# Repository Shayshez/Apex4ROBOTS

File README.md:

# Apex4ROBOTS
1u Peaks for Intellijel format

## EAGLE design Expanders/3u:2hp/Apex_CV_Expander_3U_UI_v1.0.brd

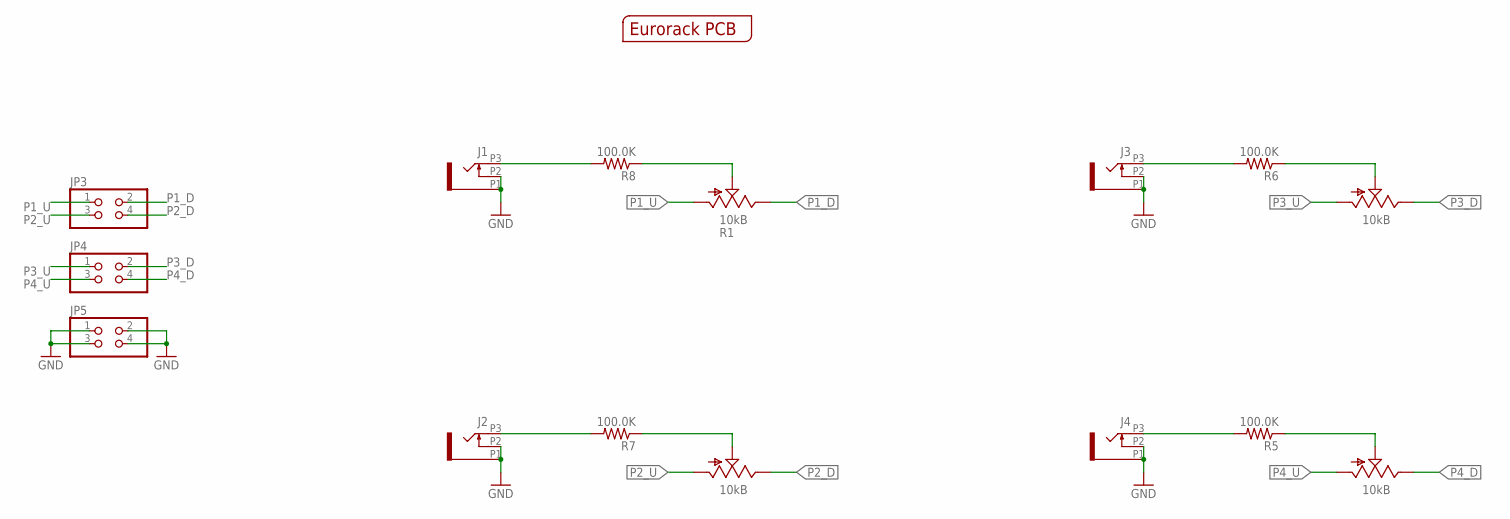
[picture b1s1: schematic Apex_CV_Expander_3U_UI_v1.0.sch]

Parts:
J1, J2, J3, J4: OG-PJ301_PJ301_THONKICONN7; OG-PJ301_WQP_PJ_301M7
JP3, JP4, JP5: PINHD-2X2; 2X02
PCB1: EURORACK_PCB2HP; EURORACK2HPPCB
R1, R2, R3, R4: 10kB; POTS_TALL_TRIMMER_POT_VERTICAL_SLOTED
R5, R6, R7, R8: 100.0K; R0603

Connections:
GND: J1.P1 (1), J1.P2 (2), J2.P1 (1), J2.P2 (2), J3.P1 (1), J3.P2 (2), J4.P1 (1), J4.P2 (2), JP5.1, JP5.2, JP5.3, JP5.4
unnamed: J1.P3 (3), R8.2
unnamed: R1.P$2 (S), R8.1
unnamed: J2.P3 (3), R7.2
unnamed: R2.P$2 (S), R7.1
unnamed: J3.P3 (3), R6.2
unnamed: R3.P$2 (S), R6.1
unnamed: J4.P3 (3), R5.2
unnamed: R4.P$2 (S), R5.1
P1_D: JP3.2, R1.P$1 (E)
P1_U: JP3.1, R1.P$3 (A)
P2_D: JP3.4, R2.P$1 (E)
P2_U: JP3.3, R2.P$3 (A)
P3_D: JP4.2, R3.P$1 (E)
P3_U: JP4.1, R3.P$3 (A)
P4_D: JP4.4, R4.P$1 (E)
P4_U: JP4.3, R4.P$3 (A)

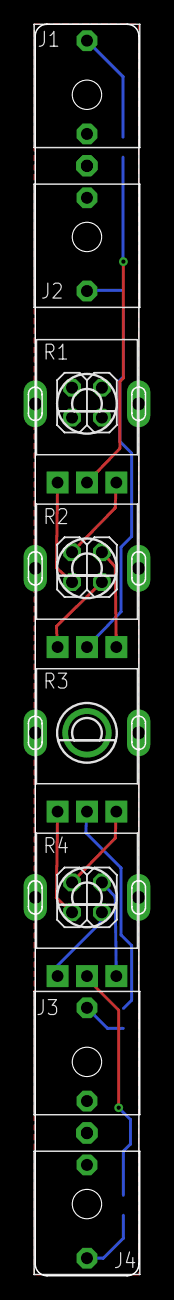
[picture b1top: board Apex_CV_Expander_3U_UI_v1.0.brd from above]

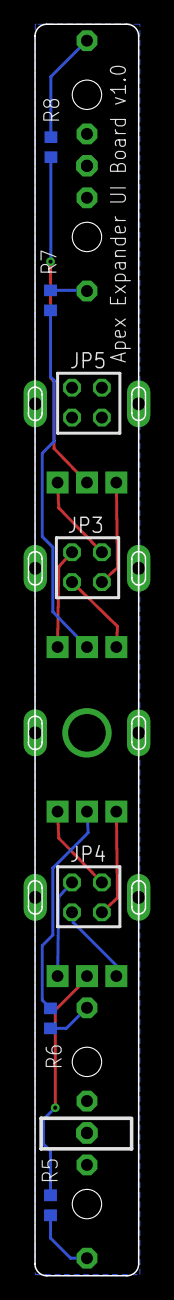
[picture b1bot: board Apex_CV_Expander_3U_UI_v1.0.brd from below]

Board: 2 copper layers, 10.0 x 106.5 mm, 16 parts (4 on the bottom side), 17 nets.

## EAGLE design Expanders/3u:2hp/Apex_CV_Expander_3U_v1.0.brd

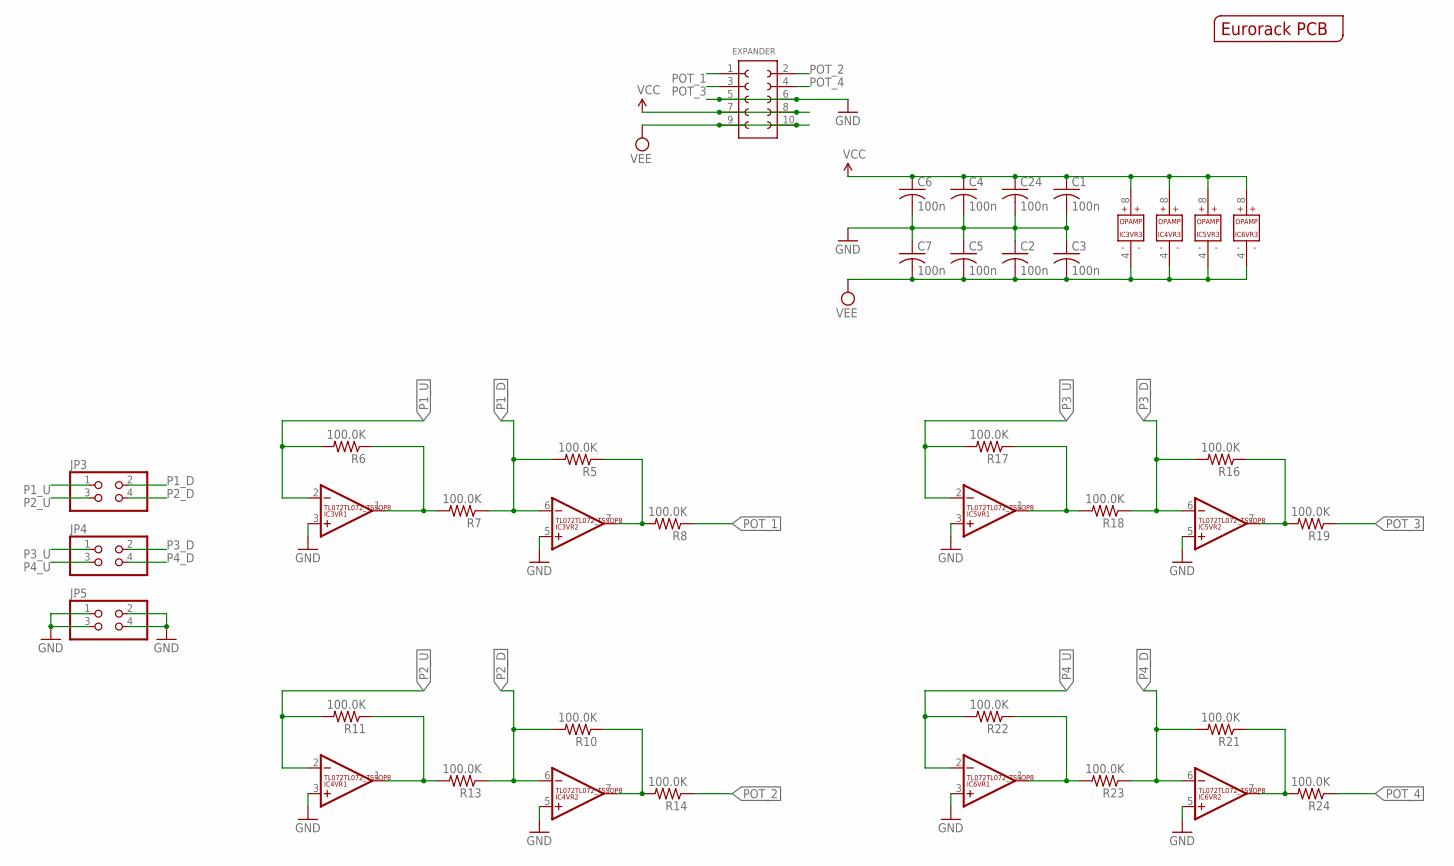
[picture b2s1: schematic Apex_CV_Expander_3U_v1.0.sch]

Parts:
C1, C2, C3, C4, C5, C6, C7, C24: 100n; C0603
EXPANDER: 61301021121
IC3, IC4, IC5, IC6: TL072TL072_TSSOP8; TL072_TSSOP8
JP3, JP4, JP5: PINHD-2X2; 2X02
PCB1: EURORACK_PCB2HP; EURORACK2HPPCB
R5, R6, R7, R8, R10, R11, R13, R14, R16, R17, R18, R19, R21, R22, R23, R24: 100.0K; R0603

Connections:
GND: C1.2, C2.1, C3.1, C4.2, C5.1, C6.2, C7.1, C24.2, EXPANDER.5 (3), EXPANDER.6 (8), IC3.3 (+IN), IC3.5 (+IN), IC4.3 (+IN), IC4.5 (+IN), IC5.3 (+IN), IC5.5 (+IN), IC6.3 (+IN), IC6.5 (+IN), JP5.1, JP5.2, JP5.3, JP5.4
unnamed: IC3.7 (OUT), R5.1, R8.2
unnamed: IC3.1 (OUT), R6.1, R7.2
unnamed: IC4.7 (OUT), R10.1, R14.2
unnamed: IC4.1 (OUT), R11.1, R13.2
unnamed: IC5.7 (OUT), R16.1, R19.2
unnamed: IC5.1 (OUT), R17.1, R18.2
unnamed: IC6.7 (OUT), R21.1, R24.2
unnamed: IC6.1 (OUT), R22.1, R23.2
P1_D: IC3.6 (-IN), JP3.2, R5.2, R7.1
P1_U: IC3.2 (-IN), JP3.1, R6.2
P2_D: IC4.6 (-IN), JP3.4, R10.2, R13.1
P2_U: IC4.2 (-IN), JP3.3, R11.2
P3_D: IC5.6 (-IN), JP4.2, R16.2, R18.1
P3_U: IC5.2 (-IN), JP4.1, R17.2
P4_D: IC6.6 (-IN), JP4.4, R21.2, R23.1
P4_U: IC6.2 (-IN), JP4.3, R22.2
POT_1: EXPANDER.1, R8.1
POT_2: EXPANDER.2 (10), R14.1
POT_3: EXPANDER.3 (2), R19.1
POT_4: EXPANDER.4 (9), R24.1
VCC: C1.1, C4.1, C6.1, C24.1, EXPANDER.7 (4), EXPANDER.8 (7), IC3.8 (V+), IC4.8 (V+), IC5.8 (V+), IC6.8 (V+)
VEE: C2.2, C3.2, C5.2, C7.2, EXPANDER.9 (5), EXPANDER.10 (6), IC3.4 (V-), IC4.4 (V-), IC5.4 (V-), IC6.4 (V-)

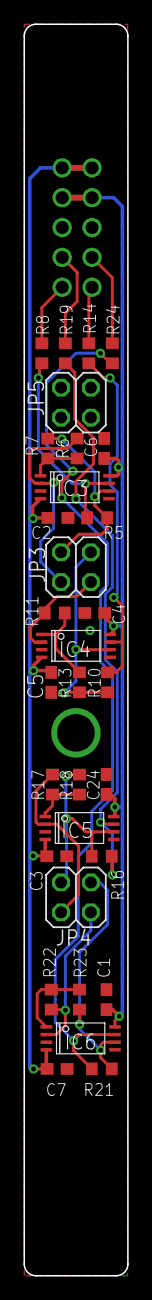
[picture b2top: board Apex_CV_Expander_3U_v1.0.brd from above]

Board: 2 copper layers, 8.8 x 106.5 mm, 33 parts (1 on the bottom side), 23 nets.

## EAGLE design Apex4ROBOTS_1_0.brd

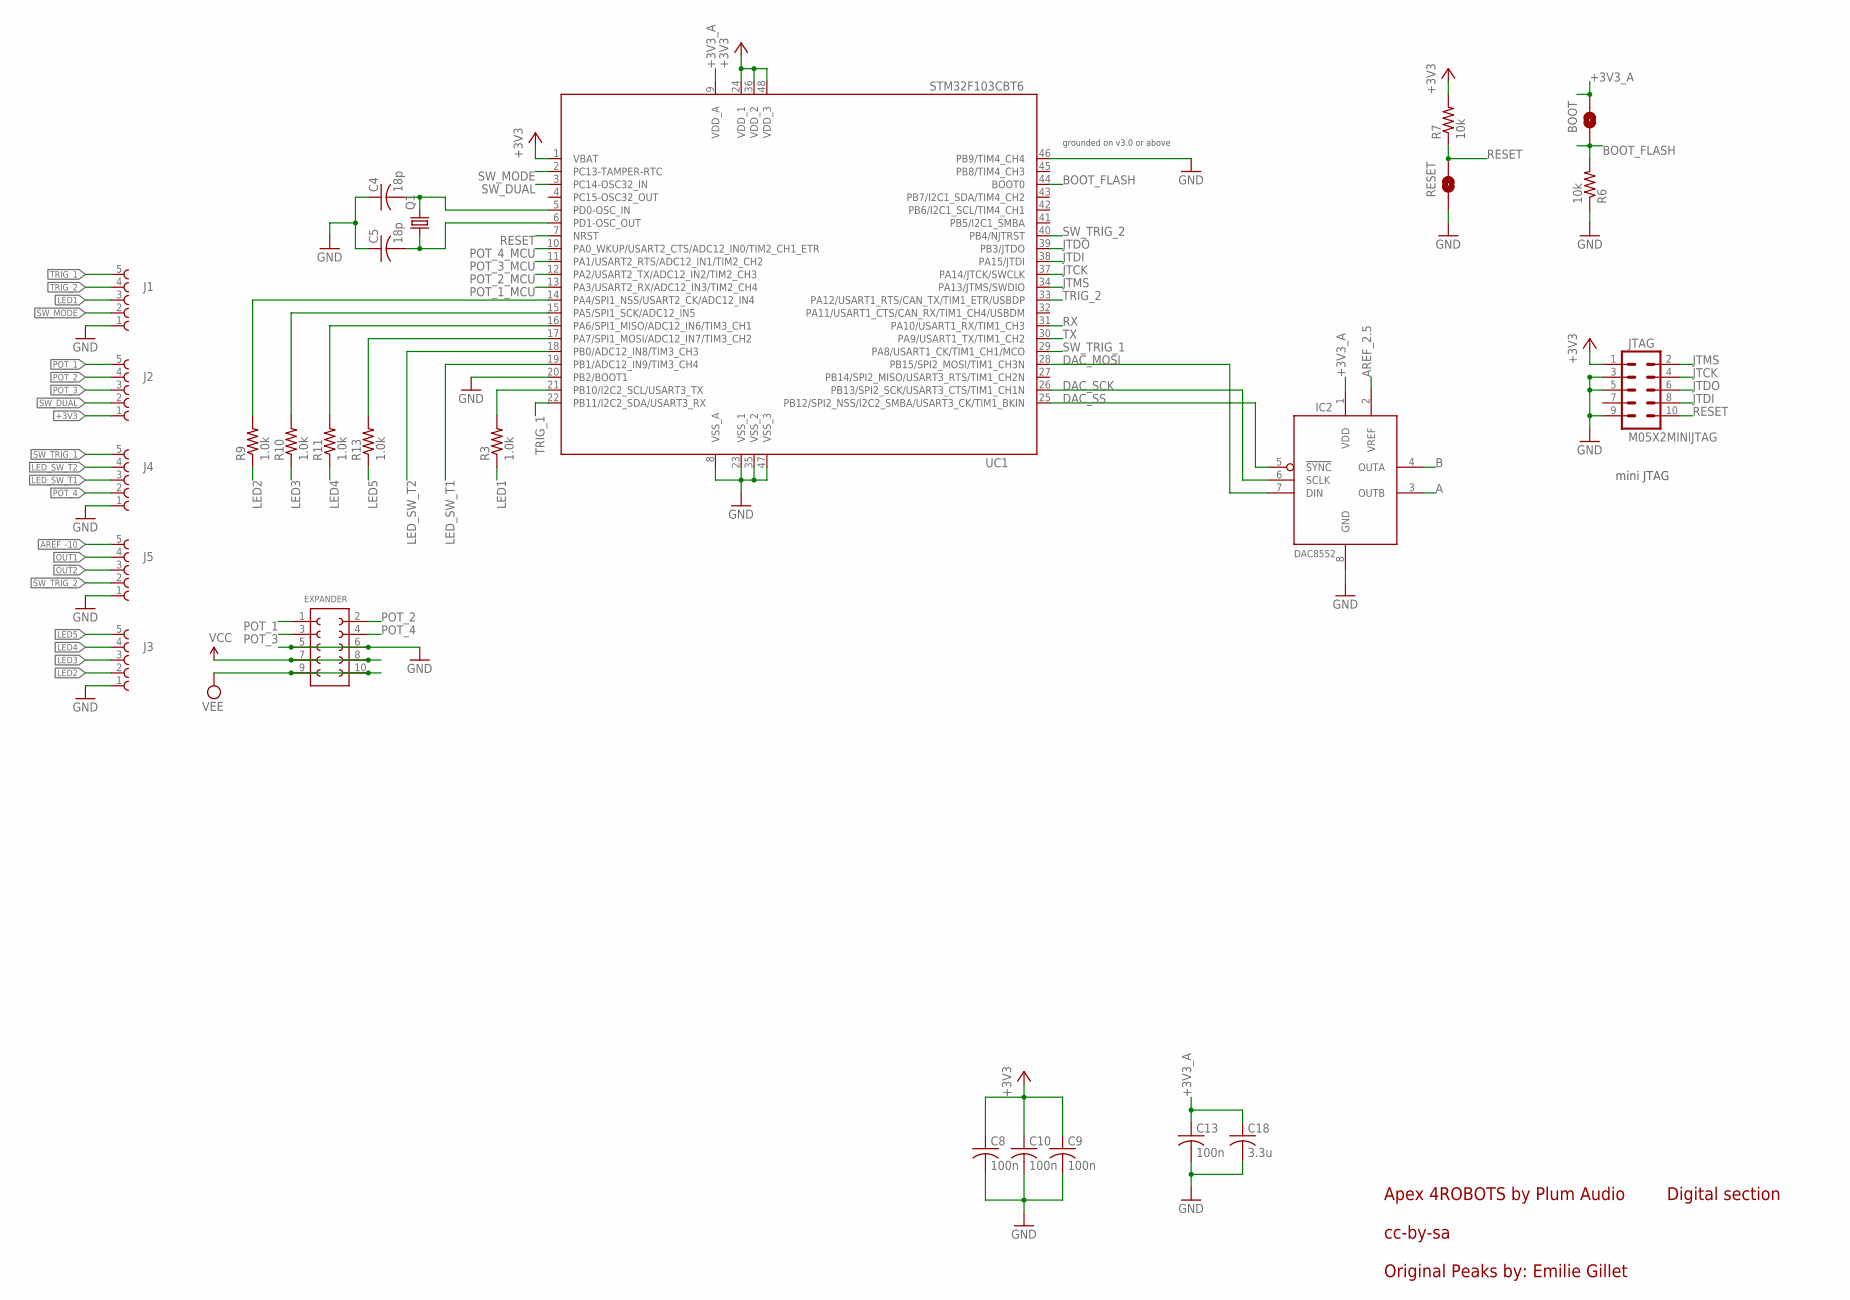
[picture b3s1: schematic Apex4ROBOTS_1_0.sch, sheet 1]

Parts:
BOOT: BOOT; SMT-JUMPER_2_NO_SILK
C4, C5: 18p; C0603
C8, C9, C10, C13: 100n; C0603
C18: 3.3u; C0603
EXPANDER: 61301021121
IC2: DAC8552; MSOP-8
J1, J2, J3, J4, J5: 61300511121
JTAG: M05X2MINIJTAG; 2X5-1.27
Q1: CRYSTAL7A; XTAL500X320X120
R3, R9, R10, R11, R13: 1.0k; R0603
R6, R7: 10k; R0603
RESET: RESET; SMT-JUMPER_2_NO_SILK
UC1: STM32F103CBT6; LQFP48

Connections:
+3V3: C8.1, C9.1, C10.1, J2.1 (5), JTAG.1, R7.2, UC1.1 (VBAT), UC1.24 (VDD_1), UC1.36 (VDD_2), UC1.48 (VDD_3); also elsewhere on the board
+3V3_A: BOOT.2, C13.1, C18.1, IC2.1 (VDD), UC1.9 (VDD_A); also elsewhere on the board
A: IC2.3 (OUTB); also elsewhere on the board
AREF_2.5: IC2.2 (VREF); also elsewhere on the board
AREF_-10: J5.5 (1); also elsewhere on the board
B: IC2.4 (OUTA); also elsewhere on the board
BOOT_FLASH: BOOT.1, R6.2, UC1.44 (BOOT0)
DAC_MOSI: IC2.7 (DIN), UC1.28 (PB15/SPI2_MOSI/TIM1_CH3N)
DAC_SCK: IC2.6 (SCLK), UC1.26 (PB13/SPI2_SCK/USART3_CTS/TIM1_CH1N)
DAC_SS: IC2.5 (!SYNC), UC1.25 (PB12/SPI2_NSS/I2C2_SMBA/USART3_CK/TIM1_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)
GND: C4.1, C5.1, C8.2, C9.2, C10.2, C13.2, C18.2, EXPANDER.5 (3), EXPANDER.6 (8), IC2.8 (GND), J1.1 (5), J3.1 (5), J4.1 (5), J5.1 (5), JTAG.3, JTAG.5, JTAG.9, R6.1, RESET.1, UC1.8 (VSS_A), UC1.20 (PB2/BOOT1), UC1.23 (VSS_1), UC1.35 (VSS_2), UC1.46 (PB9/TIM4_CH4), UC1.47 (VSS_3); also elsewhere on the board
JTCK: JTAG.4, UC1.37 (PA14/JTCK/SWCLK)
JTDI: JTAG.8, UC1.38 (PA15/JTDI)
JTDO: JTAG.6, UC1.39 (PB3/JTDO)
JTMS: JTAG.2, UC1.34 (PA13/JTMS/SWDIO)
LED1: J1.3, R3.1
LED2: J3.2 (4), R9.1
LED3: J3.3, R10.1
LED4: J3.4 (2), R11.1
LED5: J3.5 (1), R13.1
LED_SW_T1: J4.3, UC1.19 (PB1/ADC12_IN9/TIM3_CH4)
LED_SW_T2: J4.4 (2), UC1.18 (PB0/ADC12_IN8/TIM3_CH3)
unnamed: C4.2, Q1.2, UC1.5 (PD0-OSC_IN)
unnamed: C5.2, Q1.1, UC1.6 (PD1-OSC_OUT)
unnamed: R9.2, UC1.14 (PA4/SPI1_NSS/USART2_CK/ADC12_IN4)
unnamed: R10.2, UC1.15 (PA5/SPI1_SCK/ADC12_IN5)
unnamed: R11.2, UC1.16 (PA6/SPI1_MISO/ADC12_IN6/TIM3_CH1)
unnamed: R13.2, UC1.17 (PA7/SPI1_MOSI/ADC12_IN7/TIM3_CH2)
unnamed: R3.2, UC1.21 (PB10/I2C2_SCL/USART3_TX)
OUT1: J5.4 (2); also elsewhere on the board
OUT2: J5.3; also elsewhere on the board
POT_1: EXPANDER.1, J2.5 (1); also elsewhere on the board
POT_1_MCU: UC1.13 (PA3/USART2_RX/ADC12_IN3/TIM2_CH4); also elsewhere on the board
POT_2: EXPANDER.2 (10), J2.4 (2); also elsewhere on the board
POT_2_MCU: UC1.12 (PA2/USART2_TX/ADC12_IN2/TIM2_CH3); also elsewhere on the board
POT_3: EXPANDER.3 (2), J2.3; also elsewhere on the board
POT_3_MCU: UC1.11 (PA1/USART2_RTS/ADC12_IN1/TIM2_CH2); also elsewhere on the board
POT_4: EXPANDER.4 (9), J4.2 (4); also elsewhere on the board
POT_4_MCU: UC1.10 (PA0_WKUP/USART2_CTS/ADC12_IN0/TIM2_CH1_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); also elsewhere on the board
RESET: JTAG.10, R7.1, RESET.2, UC1.7 (NRST)
RX: UC1.31 (PA10/USART1_RX/TIM1_CH3)
SW_DUAL: J2.2 (4), UC1.3 (PC14-OSC32_IN)
SW_MODE: J1.2 (4), UC1.2 (PC13-TAMPER-RTC)
SW_TRIG_1: J4.5 (1), UC1.29 (PA8/USART1_CK/TIM1_CH1/MCO)
SW_TRIG_2: J5.2 (4), UC1.40 (PB4/NJTRST)
TRIG_1: J1.5 (1), UC1.22 (PB11/I2C2_SDA/USART3_RX)
TRIG_2: J1.4 (2), UC1.33 (PA12/USART1_RTS/CAN_TX/TIM1_ETR/USBDP)
TX: UC1.30 (PA9/USART1_TX/TIM1_CH2)
VCC: EXPANDER.7 (4), EXPANDER.8 (7); also elsewhere on the board
VEE: EXPANDER.9 (5), EXPANDER.10 (6); also elsewhere on the board

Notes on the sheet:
cc-by-sa
Original Peaks by: Emilie Gillet
Digital section
mini JTAG
grounded on v3.0 or above
Apex 4ROBOTS by Plum Audio

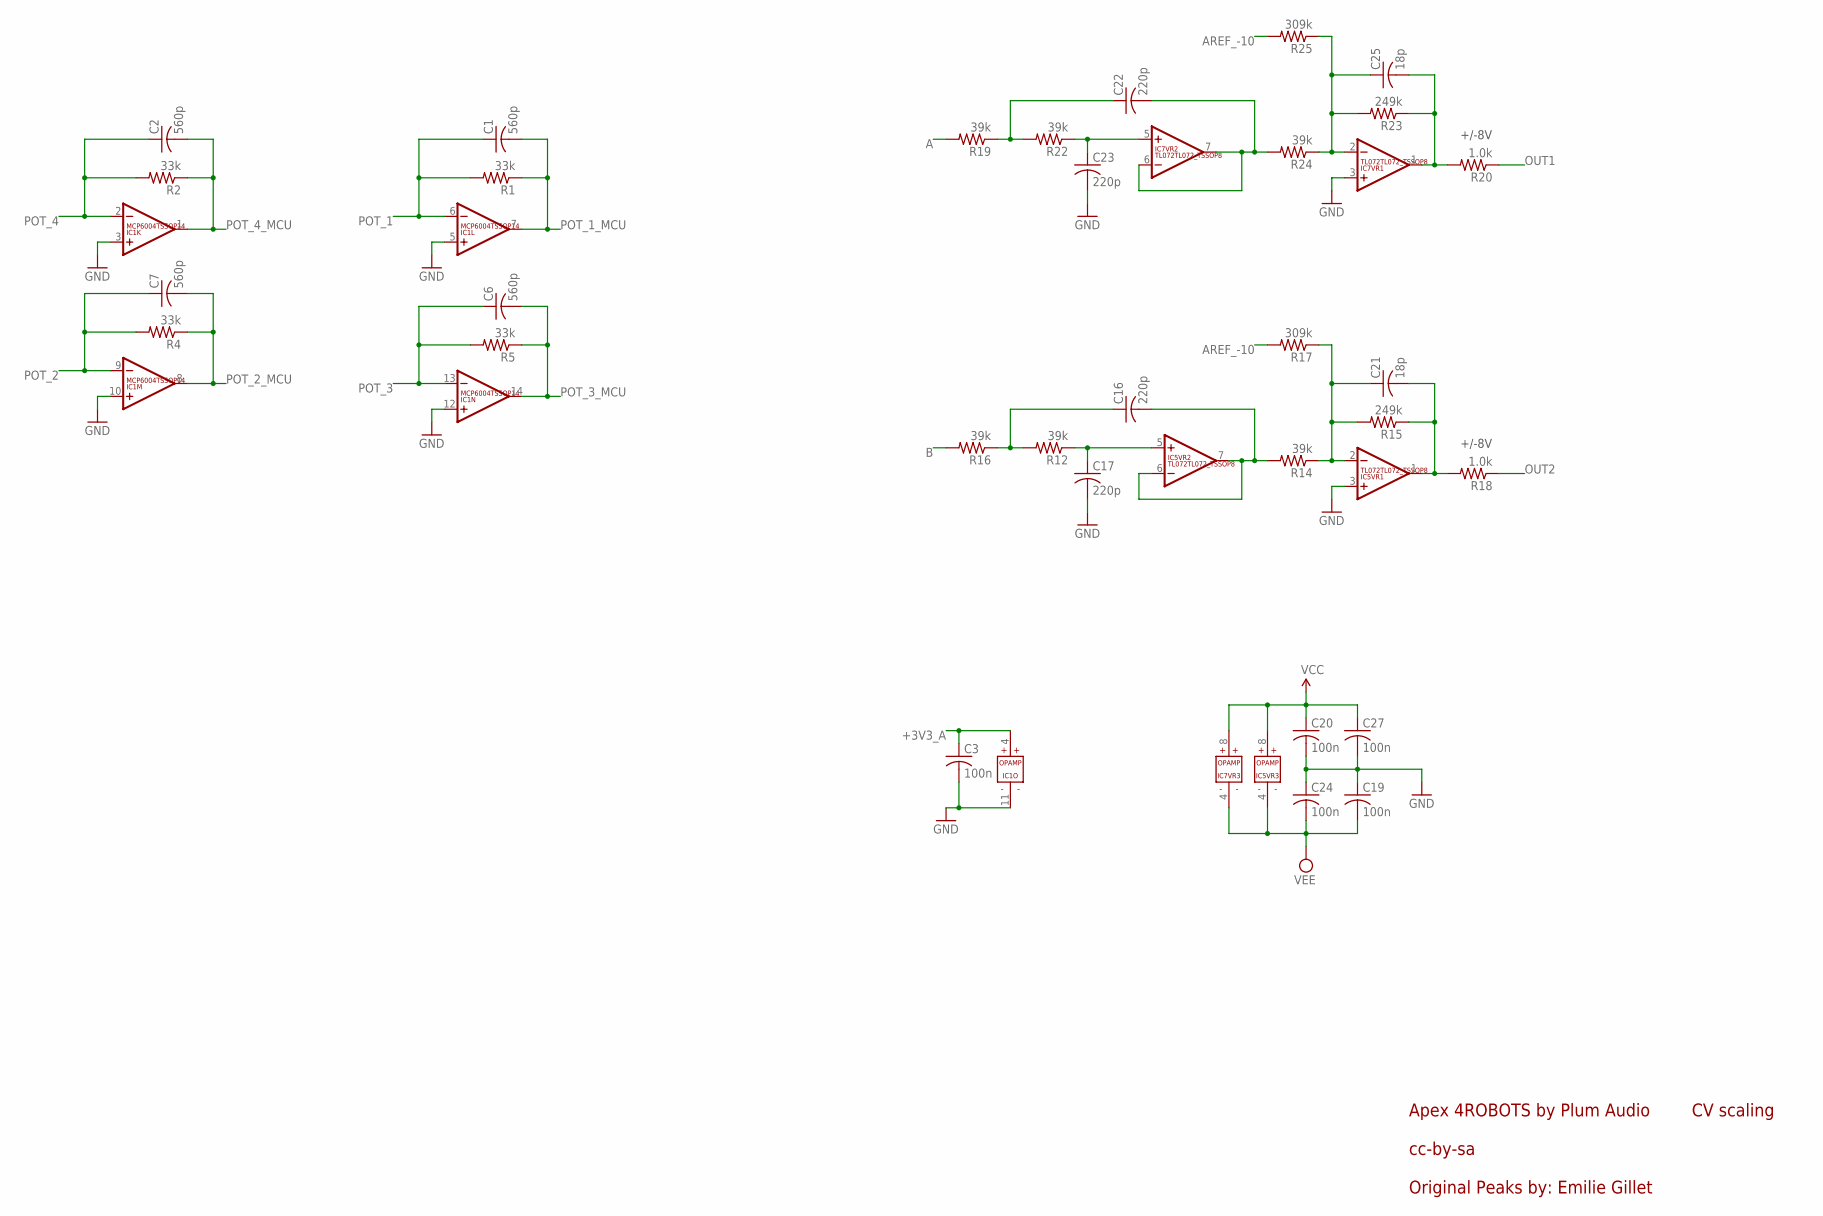
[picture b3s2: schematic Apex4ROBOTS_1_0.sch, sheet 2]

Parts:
C1, C2, C6, C7: 560p; C0603
C3, C19, C20, C24, C27: 100n; C0603
C16, C17, C22, C23: 220p; C0603
C21, C25: 18p; C0603
IC1: MCP6004TSSOP14; TSSOP14
IC5, IC7: TL072TL072_TSSOP8; TL072_TSSOP8
R1, R2, R4, R5: 33k; R0603
R12, R14, R16, R19, R22, R24: 39k; R0603
R15, R23: 249k; R0603
R17, R25: 309k; R0603
R18, R20: 1.0k; R0603

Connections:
+3V3_A: C3.1, IC1.4 (V+); also elsewhere on the board
A: R19.2; also elsewhere on the board
AREF_-10: R17.2, R25.2; also elsewhere on the board
B: R16.2; also elsewhere on the board
BI_OUT: C21.2, IC5.1 (OUT), R15.1, R18.2
BI_OUT1: C25.2, IC7.1 (OUT), R20.2, R23.1
F_CV: C21.1, IC5.2 (-IN), R14.1, R15.2, R17.1
F_CV1: C25.1, IC7.2 (-IN), R23.2, R24.1, R25.1
GND: C3.2, C17.2, C19.1, C20.2, C23.2, C24.1, C27.2, IC1.3 (+IN), IC1.5 (+IN), IC1.10 (+IN), IC1.11 (V-), IC1.12 (+IN), IC5.3 (+IN), IC7.3 (+IN); also elsewhere on the board
unnamed: C22.2, IC7.6 (-IN), IC7.7 (OUT), R24.2
unnamed: C23.1, IC7.5 (+IN), R22.1
unnamed: C22.1, R19.1, R22.2
unnamed: C16.2, IC5.6 (-IN), IC5.7 (OUT), R14.2
unnamed: C17.1, IC5.5 (+IN), R12.1
unnamed: C16.1, R12.2, R16.1
OUT1: R20.1; also elsewhere on the board
OUT2: R18.1; also elsewhere on the board
POT_1: C1.1, IC1.6 (-IN), R1.2; also elsewhere on the board
POT_1_MCU: C1.2, IC1.7 (OUT), R1.1; also elsewhere on the board
POT_2: C7.1, IC1.9 (-IN), R4.2; also elsewhere on the board
POT_2_MCU: C7.2, IC1.8 (OUT), R4.1; also elsewhere on the board
POT_3: C6.1, IC1.13 (-IN), R5.2; also elsewhere on the board
POT_3_MCU: C6.2, IC1.14 (OUT), R5.1; also elsewhere on the board
POT_4: C2.1, IC1.2 (-IN), R2.2; also elsewhere on the board
POT_4_MCU: C2.2, IC1.1 (OUT), R2.1; also elsewhere on the board
VCC: C20.1, C27.1, IC5.8 (V+), IC7.8 (V+); also elsewhere on the board
VEE: C19.2, C24.2, IC5.4 (V-), IC7.4 (V-); also elsewhere on the board

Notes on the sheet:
+/-8V
CV scaling
cc-by-sa
Original Peaks by: Emilie Gillet
Apex 4ROBOTS by Plum Audio

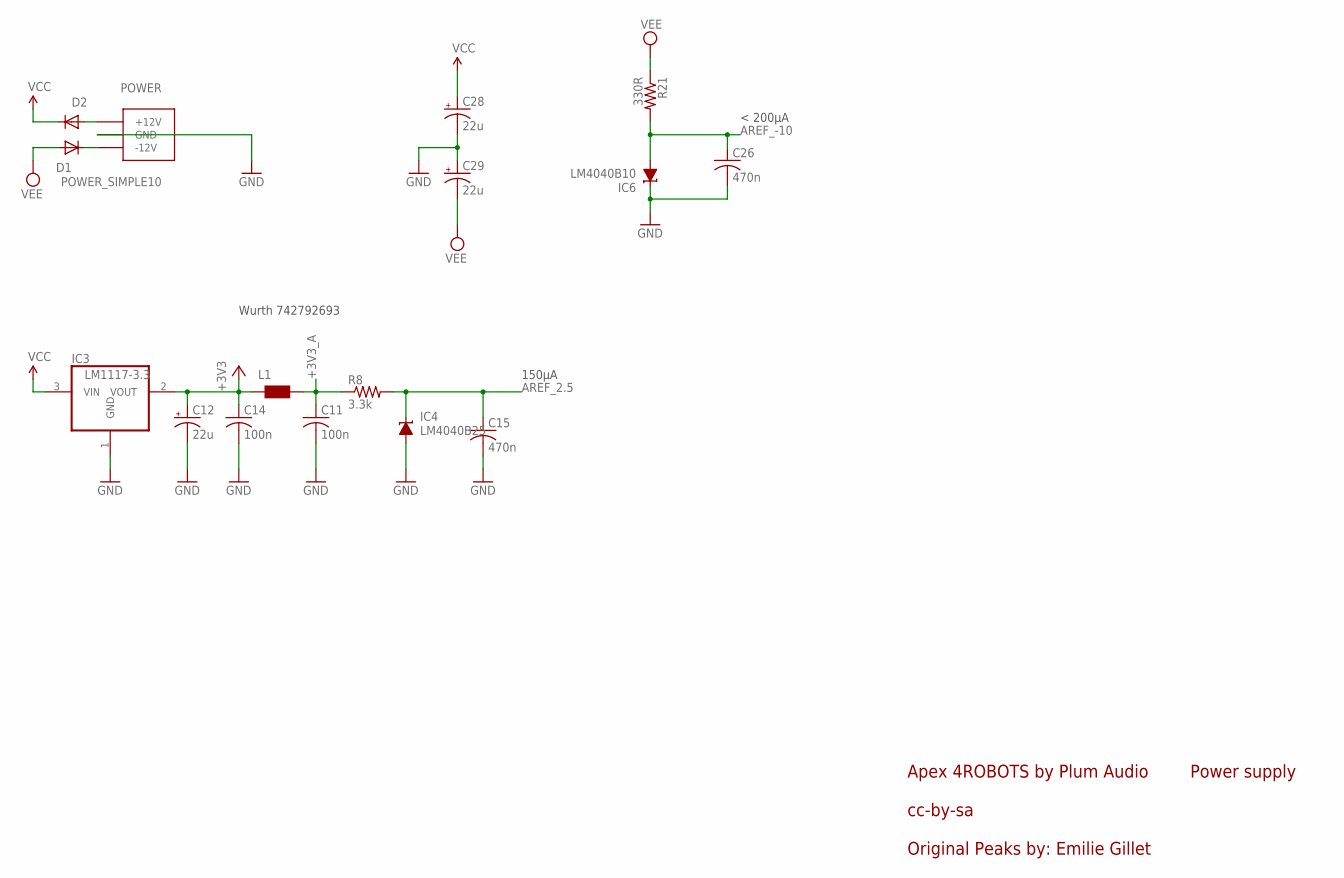
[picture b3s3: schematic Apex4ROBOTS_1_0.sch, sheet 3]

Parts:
C11, C14: 100n; C0603
C12, C28, C29: 22u; PANASONIC_C
C15, C26: 470n; C0603
D1, D2: 1N5819HW; SOD123
IC3: LM1117-3.3; SOT223
IC4: LM4040B25; DBZ_R-PDSO-G3
IC6: LM4040B10; DBZ_R-PDSO-G3
L1: WE-CBF_0603; 0603
POWER: POWER_SIMPLE10; POWER_10
R8: 3.3k; R0603
R21: 330R; R0603

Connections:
+3V3: C12.+, C14.1, IC3.2 (VOUT), L1.1; also elsewhere on the board
+3V3_A: C11.1, L1.2, R8.1; also elsewhere on the board
AREF_2.5: C15.1, IC4.1 (C), R8.2; also elsewhere on the board
AREF_-10: C26.1, IC6.2 (A), R21.2; also elsewhere on the board
GND: C11.2, C12.-, C14.2, C15.2, C26.2, C28.-, C29.+, IC3.1 (GND), IC4.2 (A), IC6.1 (C), POWER.3 (GND), POWER.4 (GND), POWER.5 (GND), POWER.6 (GND), POWER.7 (GND), POWER.8 (GND); also elsewhere on the board
unnamed: D2.A, POWER.9 (+12V), POWER.10 (+12V)
unnamed: D1.C, POWER.1 (-12V), POWER.2 (-12V)
VCC: C28.+, D2.C, IC3.3 (VIN); also elsewhere on the board
VEE: C29.-, D1.A, R21.1; also elsewhere on the board

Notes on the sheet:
Power supply
Wurth 742792693
< 200µA
150µA
cc-by-sa
Original Peaks by: Emilie Gillet
Apex 4ROBOTS by Plum Audio

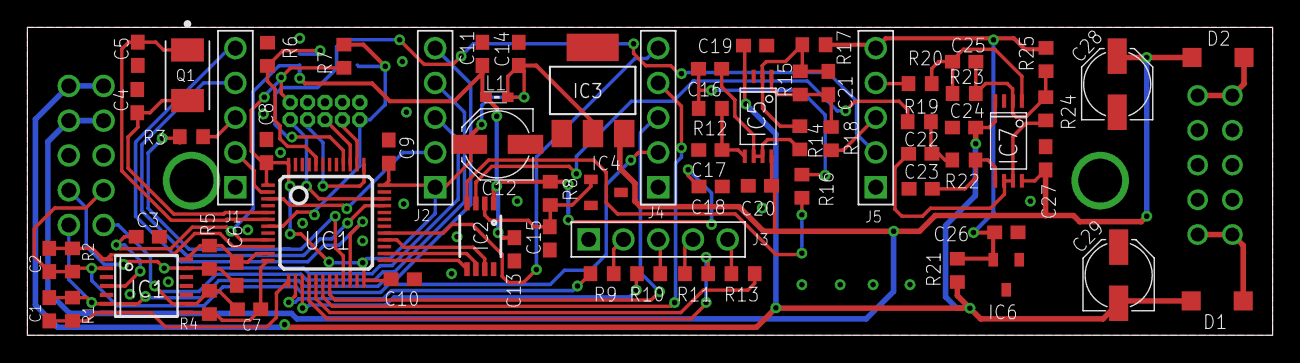
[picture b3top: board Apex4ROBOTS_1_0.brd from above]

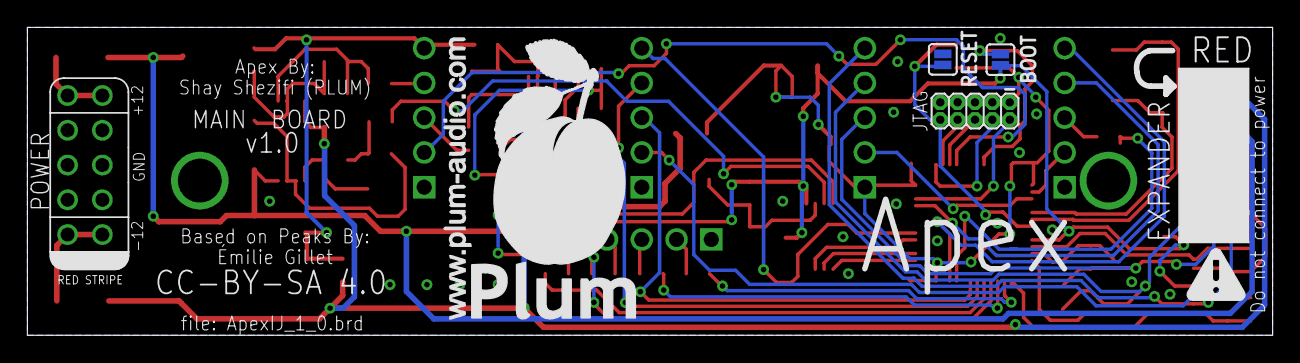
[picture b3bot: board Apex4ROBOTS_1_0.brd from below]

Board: 2 copper layers, 91.0 x 22.5 mm, 76 parts (5 on the bottom side), 60 nets.

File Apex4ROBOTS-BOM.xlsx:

Qty | Value | Device | Package | Parts | Description
1 | 330R | R-US_R0603 | R0603 | R21 | RESISTOR, American symbol
7 | 1.0k | R-US_R0603 | R0603 | R3, R9, R10, R11, R13, R18, R20 | RESISTOR, American symbol
1 | 3.3k | R-US_R0603 | R0603 | R8 | RESISTOR, American symbol
2 | 10k | R-US_R0603 | R0603 | R6, R7 | RESISTOR, American symbol
4 | 33k | R-US_R0603 | R0603 | R1, R2, R4, R5 | RESISTOR, American symbol
6 | 39k | R-US_R0603 | R0603 | R12, R14, R16, R19, R22, R24 | RESISTOR, American symbol
2 | 249k | R-US_R0603 | R0603 | R15, R23 | RESISTOR, American symbol
2 | 309k | R-US_R0603 | R0603 | R17, R25 | RESISTOR, American symbol
4 | 18p | C-USC0603 | C0603 | C4, C5, C21, C25 | CAPACITOR, American symbol
4 | 220p | C-USC0603 | C0603 | C16, C17, C22, C23 | CAPACITOR, American symbol
4 | 560p | C-USC0603 | C0603 | C1, C2, C6, C7 | CAPACITOR, American symbol
11 | 100n | C-USC0603 | C0603 | C3, C8, C9, C10, C11, C13, C14, C19, C20, C24, C27 | CAPACITOR, American symbol
2 | 470n | C-USC0603 | C0603 | C15, C26 | CAPACITOR, American symbol
1 | 3.3u | C-USC0603 | C0603 | C18 | CAPACITOR, American symbol
3 | 22u | CPOL-USC | PANASONIC_C | C12, C28, C29 | POLARIZED CAPACITOR, American symbol
1 | EMI Bead | WE-CBF_0603 | 603 | L1 | SMD EMI Suppression Ferrite Beads
2 | 1N5819HW | DIODE-SOD123 | SOD123 | D1, D2 | DIODE
1 | LM1117-3.3 | REG1117 | SOT223 | IC3 | 800mA and 1A Low Dropout (LDO) Positive Regulator
1 | DAC8552 | DAC8552 | MSOP-8 | IC2
1 | LM4040B10 | LM4041B12DBZ | DBZ_R-PDSO-G3 | IC6 | PRECISION MICROPOWER SHUNT VOLTAGE REFERENCE
1 | LM4040B25 | LM4041B12DBZ | DBZ_R-PDSO-G3 | IC4 | PRECISION MICROPOWER SHUNT VOLTAGE REFERENCE
1 | MCP6004TSSOP14 | MCP6004TSSOP14 | TSSOP14 | IC1
2 | TL072TL072_TSSOP8 | TL072TL072_TSSOP8 | TL072_TSSOP8 | IC5, IC7
1 | STM32F103CBT6 | STM32F103CB | LQFP48 | UC1
1 | 8.0Mhz Crystal | CRYSTAL7A | XTAL500X320X120 | Q1 | CRYSTAL
5 |  | 61300511121 | 61300511121 | J1, J2, J3, J4, J5 | WR-PHD 2.54mm Pin Header, 5 Pin =>Code : Con_BTB_PHD_2.54_1_THT_61300511121
1 |  | 61301021121 | 61301021121 | EXPANDER | WR-PHD 2.54mm Dual Pin Header, 10 Pins =>Code : Con_BTB_PHD_2.54_2_61301021121
1 | M05X2MINIJTAG | M05X2MINIJTAG | 2X5-1.27 | JTAG | Header 5x2
1 | POWER_SIMPLE10 | POWER_SIMPLE10 | POWER_10 | POWER

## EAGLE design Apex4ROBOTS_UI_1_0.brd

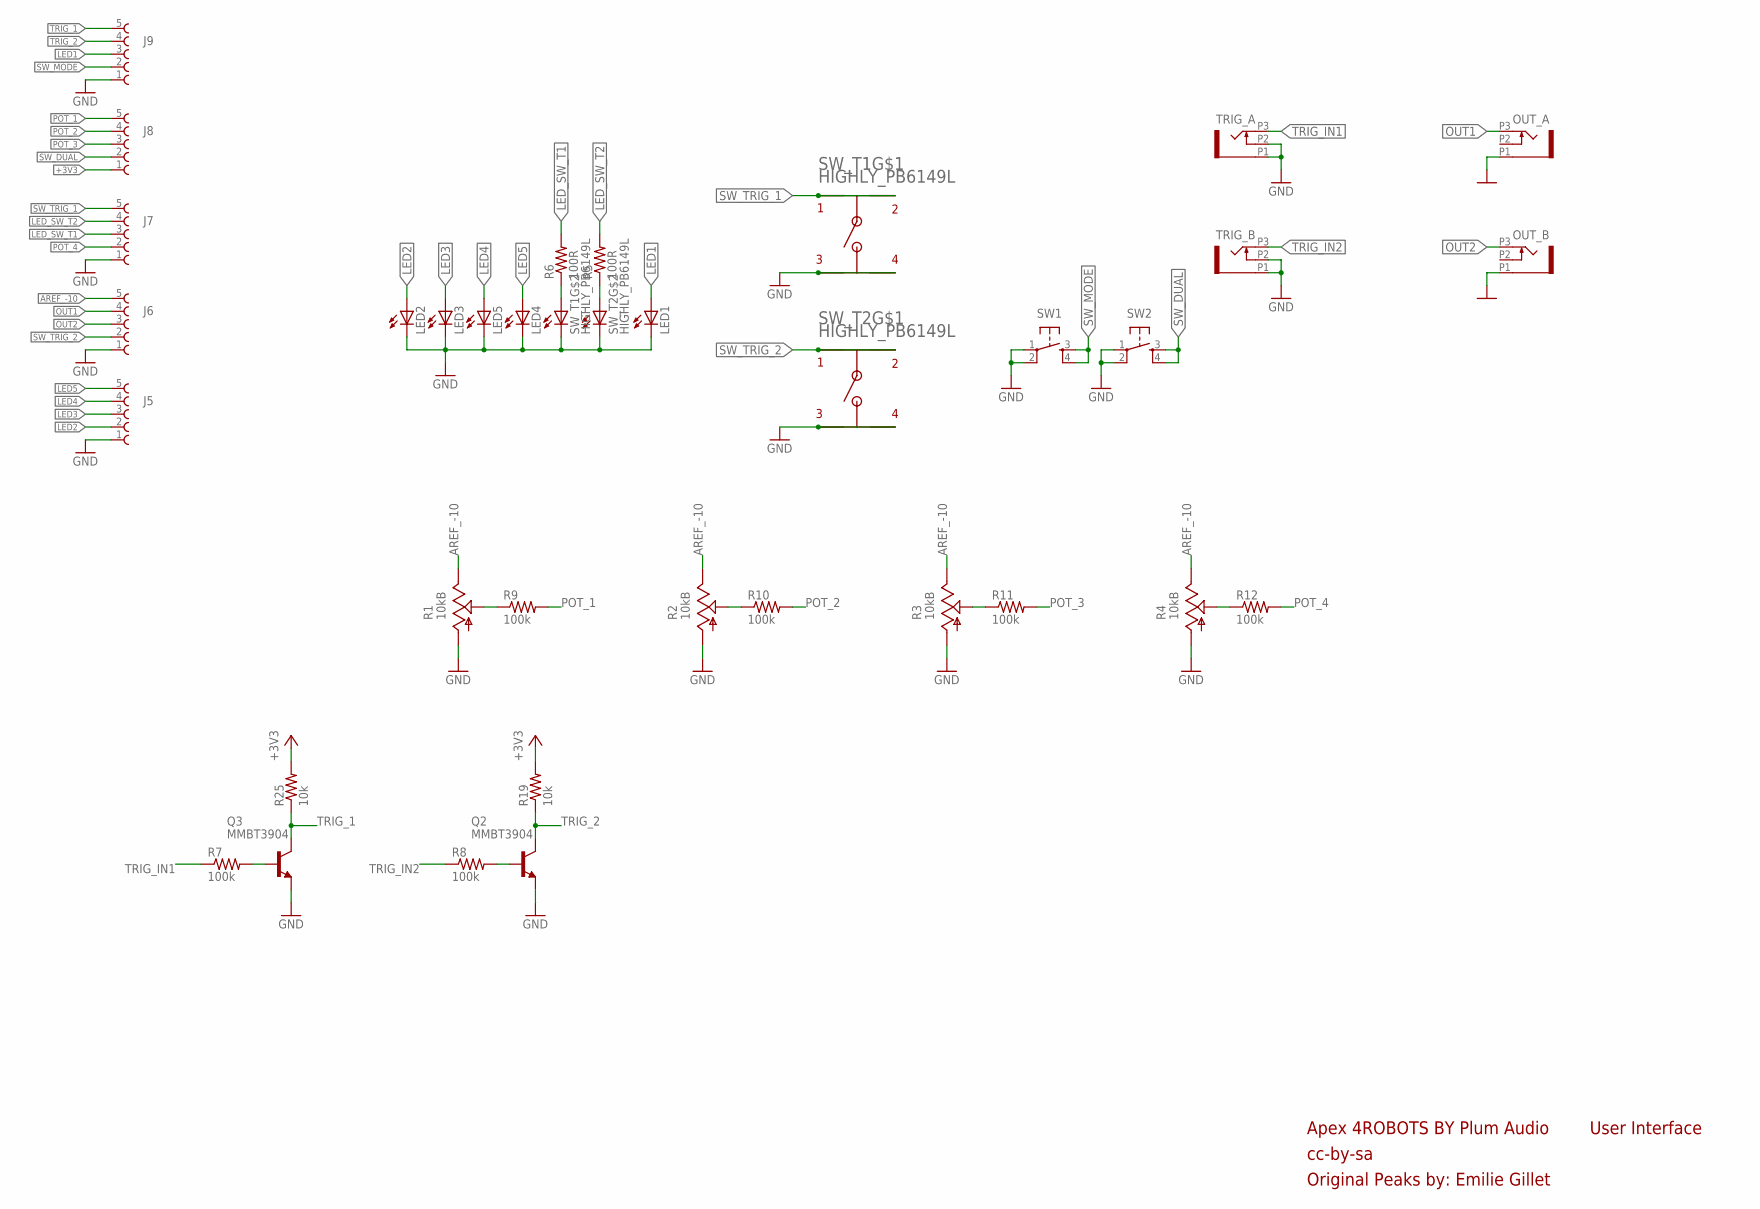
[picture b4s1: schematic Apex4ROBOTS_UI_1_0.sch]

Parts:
J5, J6, J7, J8, J9: 61300511121
LED1, LED2, LED3, LED4, LED5: LED3MM
OUT_A: OG-PJ301_PJ301_THONKICONN6; OG-PJ301_WQP_PJ_301M6
OUT_B: OG-PJ301_PJ301_THONKICONN6; OG-PJ301_WQP_PJ_301M6
Q2, Q3: MMBT3904; SOT23-BEC
R1, R2, R3, R4: 10kB; POTS_TALL_TRIMMER_POT_VERTICAL_SLOTED
R5, R6: 100R; R0603
R7, R8, R9, R10, R11, R12: 100k; R0603
R19, R25: 10k; R0603
SW1, SW2: TAC_SWITCHPTH; TACTILE-PTH
SW_T1, SW_T2: HIGHLY_PB6149L; HIGHLY_PB64149L
TRIG_A: OG-PJ301_PJ301_THONKICONN6; OG-PJ301_WQP_PJ_301M6
TRIG_B: OG-PJ301_PJ301_THONKICONN6; OG-PJ301_WQP_PJ_301M6

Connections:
+3V3: J8.1 (5), R19.2, R25.2
AREF_-10: J6.5 (1), R1.P$1 (E), R2.P$1 (E), R3.P$1 (E), R4.P$1 (E)
GND: J5.1 (5), J6.1 (5), J7.1 (5), J9.1 (5), LED1.K (C), LED2.K (C), LED3.K (C), LED4.K (C), LED5.K (C), OUT_A.P1 (1), OUT_B.P1 (1), Q2.E, Q3.E, R1.P$3 (A), R2.P$3 (A), R3.P$3 (A), R4.P$3 (A), SW1.1, SW1.2, SW2.1, SW2.2, SW_T1.L2, SW_T1.P$3, SW_T1.P$4, SW_T2.L2, SW_T2.P$3, SW_T2.P$4, TRIG_A.P1 (1), TRIG_A.P2 (2), TRIG_B.P1 (1), TRIG_B.P2 (2)
LED1: J9.3, LED1.A
LED2: J5.2 (4), LED2.A
LED3: J5.3, LED3.A
LED4: J5.4 (2), LED5.A
LED5: J5.5 (1), LED4.A
LED_SW_T1: J7.3, R6.2
LED_SW_T2: J7.4 (2), R5.2
unnamed: R5.1, SW_T2.L1
unnamed: R6.1, SW_T1.L1
unnamed: R1.P$2 (S), R9.1
unnamed: R2.P$2 (S), R10.1
unnamed: R3.P$2 (S), R11.1
unnamed: R4.P$2 (S), R12.1
unnamed: Q2.B, R8.2
unnamed: Q3.B, R7.2
OUT1: J6.4 (2), OUT_A.P3 (3)
OUT2: J6.3, OUT_B.P3 (3)
POT_1: J8.5 (1), R9.2
POT_2: J8.4 (2), R10.2
POT_3: J8.3, R11.2
POT_4: J7.2 (4), R12.2
SW_DUAL: J8.2 (4), SW2.3, SW2.4
SW_MODE: J9.2 (4), SW1.3, SW1.4
SW_TRIG_1: J7.5 (1), SW_T1.P$1, SW_T1.P$2
SW_TRIG_2: J6.2 (4), SW_T2.P$1, SW_T2.P$2
TRIG_1: J9.5 (1), Q3.C, R25.1
TRIG_2: J9.4 (2), Q2.C, R19.1
TRIG_IN1: R7.1, TRIG_A.P3 (3)
TRIG_IN2: R8.1, TRIG_B.P3 (3)

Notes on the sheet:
cc-by-sa
Original Peaks by: Emilie Gillet
User Interface
Apex 4ROBOTS BY Plum Audio

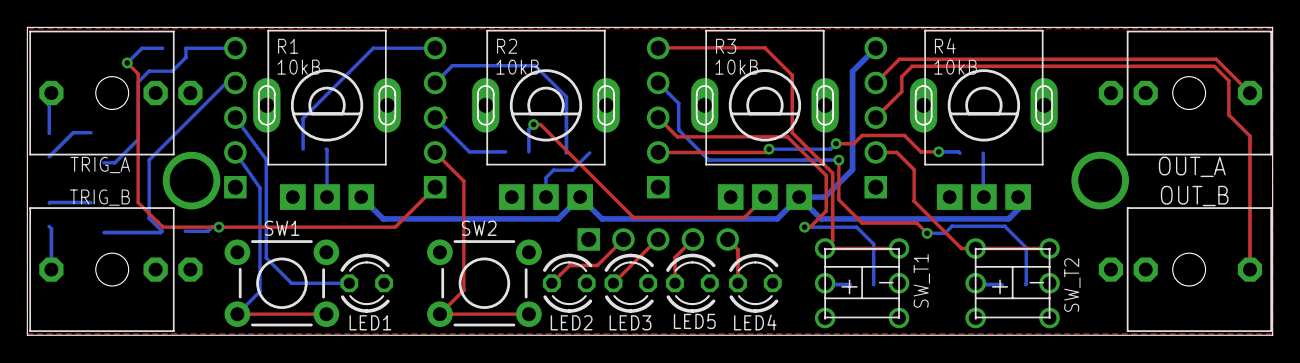
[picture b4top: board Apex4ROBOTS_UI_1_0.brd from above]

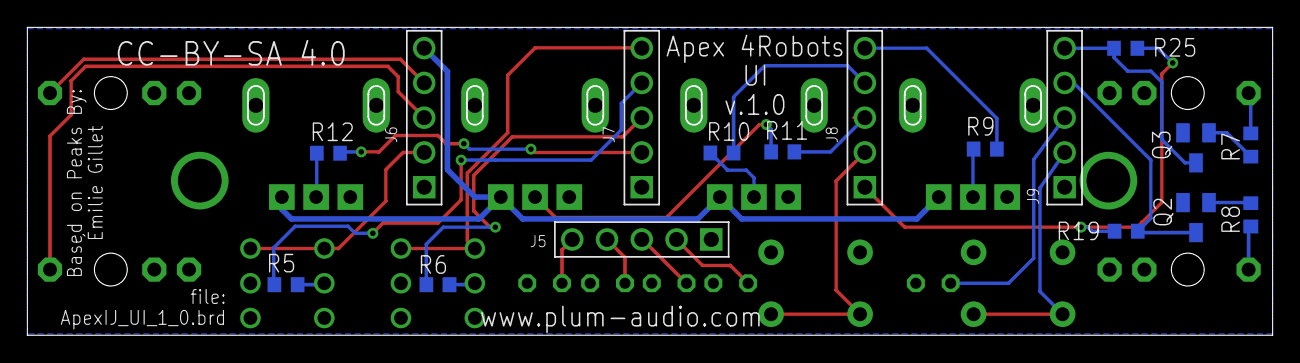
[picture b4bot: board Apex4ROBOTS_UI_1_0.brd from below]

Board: 2 copper layers, 90.9 x 22.4 mm, 34 parts (17 on the bottom side), 32 nets.

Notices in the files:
Apex4ROBOTS_1_0.brd:
CC-BY-SA 4.0
parts and their libraries:
SparkFun-Jumpers: Licensing: Creative Commons ShareAlike 4.0 International - https://creativecommons.org/licenses/by-sa/4.0
Wurth_Elektronik_Electromechanic_Board_t: Copyright: Würth Elektronik
